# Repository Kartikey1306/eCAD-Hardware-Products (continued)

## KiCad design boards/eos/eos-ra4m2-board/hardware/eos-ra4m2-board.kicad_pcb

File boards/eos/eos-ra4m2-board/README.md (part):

# EoS RA4M2 Board

An 80 × 170 mm, two-layer RA4M2 development board with Uno R3 shield sockets,
SPI and I²C Pmod ports, a GPIO access header, USB device, USB-UART and SWD.
Designed by Kartikeydheer Srivastava.
All rights reserved: not open source, and not under this repository's MIT licence.
Anyone may view it, clone this repository and run its tests; anything more needs
Kartikeydheer Srivastava's written permission (kartikeydheer@gmail.com). EmbeddedOS (EoS) Research Foundation has a limited, revocable
permission. See [LICENSE.txt](LICENSE.txt) and [the licence summary](../README.md#licence).

A board for the same job as Renesas EK-RA4M2; an original design, not a copy:
no design file of the vendor's was used; the header positions come from the
published Uno R3 relative dimensions in Matthew Beckler's dimension drawing
v1.05 and Digilent's Pmod Interface Specification 1.3.0, with original placement
on the board. The 80 × 170 mm overall dimensions come from the EK-RA4M2 user
manual, R20UT4815EG0100 §3. Its mounting and connector coordinates are not
dimensioned there, so this board does not claim enclosure or mounting-pattern
compatibility. The MCU assignments are original and require their own firmware
configuration.

| Top | Bottom |
|---|---|
|  |  |

## What is on it

| Block | Parts, values and source |
|---|---|
| MCU | Renesas R7FA4M2AD3CFP, Cortex-M33, 100 MHz, 512 KB code flash, 8 KB data flash, 128 KB SRAM, LQFP-100. Pins: R01DS0367EJ0150 Table 1.17, LQFP100 column. |
| Digital supply | 100 nF at each VCC pin and VCC_USB; 220 nF C0G at VCL; VBATT tied to 3.3 V. R01UH0892 Table 45.1 and R01AN5988 Table 1. |
| Analog supply | Bourns MH1608-221Y 220 Ω ferrite; 10 µF + 10 nF bulk/filter capacitors, 100 nF at AVCC0 and VREFH0; VREFH also tied to this supply. R01UH0892 Figure 37.34. |
| Clocks | NDK NX3225GA 16 MHz, CL 8 pF, with two 6 pF loads; Abracon ABS07 32.768 kHz, CL 9 pF, with two 15 pF loads. R01AN7202 Rev.1.02 Group 1 Tables 4.1.1/4.2.1; select 8.1–16 MHz main drive and standard CL sub-clock drive. |
| Device USB (J1) | RA4M2 USBFS, USB-C sink, 5.1 kΩ on each CC pin, 27 Ω on D+/D−, SP0503BAHTG ground-only ESD and 500 mA PTC. VBUS sense uses 18 kΩ/30 kΩ plus 1 µF, adapted from R01UH0892 Figure 26.3 for a 5.5 V maximum input. |
| Debug USB (J2) | CP2102N-A02-GQFN24 on SCI9 P109/P110, also the ROM serial boot pins. Powered by board 3.3 V with VREGIN tied to VDD; 100 nF local bypass and 4.7 µF bulk capacitors, 1 kΩ reset pull-up. VBUS divider 22.1 kΩ/47.5 kΩ and 5.1 kΩ bleed; SP0503BAHTG ESD. CP2102N data sheet Figures 2.3/2.6, R01UH0892 Table 44.27. |
| Power selection | TPS2116 prefers J2, otherwise J1, with reverse blocking between ports. 27 kΩ/10 kΩ PR1 divider, MODE to VIN1, 1 µF per input and 100 µF polymer output. TI SLVSFG1A §§7.3.4, 7.6.1.1 and 9. |
| Regulator | TPS7A9101, 3.57 kΩ/1.15 kΩ feedback for nominal 3.283 V, 22 µF input, 10 µF output, 10 nF NR/SS for calculated 0.80–2.2 ms ramp. TI SBVS282A Table 7-1, Equation 6 and §7.1.3; RA4M2 Table 2.9. |
| Debug and boot | Standard Arm 10-pin SWD header J9, replacing the proprietary on-board probe. 10 kΩ RES/NMI pull-ups, reset button, no reset capacitor. JP1 grounds MD through 1.5 kΩ for boot mode; otherwise its internal pull-up selects normal execution. R20UT4686 Figures 2.7/2.9 and R01AN5988 §§3/6. |
| User interface | User button P408/IRQ7 with 10 kΩ pull-up; red P409, green P410 and yellow P411 LEDs, about 2 mA each using 750/680/680 Ω. Green supply LED uses 680 Ω. Kingbright DSAO7432/7433/7434. |
| Expansion | Uno R3 sockets, Type 2A SPI Pmod and Type 6A I²C Pmod; 2.2 kΩ I²C pull-ups, removable by cutting JP2. TI SLVA689A gives 161 pF maximum bus capacitance for 400 kHz with these pulls. J10 exposes 33 remaining GPIOs. |

Both USB ports and the MCU share the same 3.3 V supply. The UART bridge therefore
cannot be unpowered while MCU TX is driven. Its separate VBUS sense prevents an
asserted USB pull-up after its cable is unplugged. The ground-only ESD parts do
not create a D+ to VBUS path. Configure CP2102N descriptors and MCU USB firmware
for the board's actual power consumption.

The device-port divider produces at most 3.47 V at 5.5 V with 1% resistor
extremes, below the MCU's 3.6 V limit when VCC is absent. At 4.4 V it produces at
least 2.729 V, above the worst-case 2.658 V input-high threshold for this supply.

## Headers and firmware

All logic is **3.3 V**. J5's 3V3, IOREF and 5V pins, both Pmod supplies and J10's
3V3 pins are outputs. Do not apply external power through them. AREF and VIN are
unconnected. Do not drive GPIOs while the board is unpowered.

| Shield signal | RA4M2 port/function |
|---|---|
| D0, D1 | P113 RXD2, P112 TXD2 |
| D2, D3, D4 | P111, P114 GTIOC2B, P609 |
| D5, D6, D7 | P608 GTIOC4B, P115 GTIOC4A, P610 |
| D8, D9, D10 | P603, P602 GTIOC7B, P103 |
| D11, D12, D13 | P101 MOSI0, P100 MISO0, P102 SCK0 (SCI0 simple SPI) |
| SDA, SCL | P401 SDA0_A, P400 SCL0_A (IIC0) |
| A0–A5 | P005–P000, respectively (AN005–AN000) |

J3, pin 1 to 10: D8, D9, D10, D11, D12, D13, GND, AREF (open), SDA, SCL.
J4, pin 1 to 8: D0–D7. J5, pin 1 to 8: NC, IOREF, RESET, 3V3, 5V, GND, GND,
VIN (open). J6, pin 1 to 6: A0–A5.

| Pmod pin | J7 Type 2A SPI | J8 Type 6A I²C |
|---|---|---|
| 1 | P500, GPIO chip select | P403, interrupt |
| 2 | P101, MOSI0 | P402, reset |
| 3 | P100, MISO0 | P400, SCL0_A |
| 4 | P102, SCK0 | P401, SDA0_A |
| 5, 11 | GND | GND |
| 6, 12 | 3V3 | 3V3 |
| 7 | P501, interrupt | P404 |
| 8 | P502, reset | P405 |
| 9 | P503, second chip select | P505 |
| 10 | P504, third chip select | NC |

Pmod numbering differs from KiCad's odd/even connector-pad numbering. These
are the Pmod mating pin numbers; the schematic part description records the
pad conversion. Each socket's square pad is the footprint's pad 1, which is
Pmod pin 6 (3V3), not Pmod pin 1. Pmod pin 1 is pad 11, marked by a silkscreen
"1" beside it. The SPI and I²C signals are shared with the shield sockets.
Avoid two peripherals using the same chip-select or I²C address.

J9 uses the standard Cortex Debug SWD pinout: 1 VTref, 2 SWDIO/P108, 3 GND,
4 SWCLK/P300, 5 GND, 6 SWO/P109, 7 key/open, 8 open, 9 GND detect, 10 RES.
SWO and the UART's TXD9 share P109: select one function in firmware. SWO trace
bytes can reach the UART receiver when trace is selected; this is not a second
independent console.

J9 follows the Arm pinout, not Renesas's combined debug and serial pinout
(R01UH0892 Table 44.32), which puts P201/MD on pin 4 and P110/RXD9 on pin 8. SWD
on J9 flashes and debugs the MCU. The TrustZone IDAU boundary settings can be
written only through the serial programming interface (R01UH0892 §44), so an
E2 or E2 Lite on J9 cannot set them. To program them, fit JP1, reset the board,
and run Renesas Flash Programmer over the CP2102N on J2 in SCI boot mode.

J10 follows ordinary odd/even 2×20 numbering, pin 1 marked on the PCB:

| Odd pin | Signal | Even pin | Signal |
|---:|---|---:|---|
| 1 | P006 | 2 | P007 |
| 3 | P008 | 4 | P013 |
| 5 | P014 | 6 | P015 |
| 7 | P406 | 8 | P412 |
| 9 | P413 | 10 | P414 |
| 11 | P415 | 12 | P708 |
| 13 | P104 | 14 | P105 |
| 15 | P106 | 16 | P107 |
| 17 | P600 | 18 | P601 |
| 19 | P205 | 20 | P206 |
| 21 | P207 | 22 | P208 |
| 23 | P209 | 24 | P210 |
| 25 | P211 | 26 | P214 |
| 27 | P301 | 28 | P302 |
| 29 | P303 | 30 | P304 |
| 31 | P305 | 32 | P306 |
| 33 | P307 | 34 | GND |
| 35 | 3V3 | 36 | GND |
| 37 | 3V3 | 38 | GND |
| 39 | 3V3 | 40 | GND |

J10 pins 1–6 are PORT0 pins (P006, P007, P008, P013, P014, P015). While the
ADC's high-precision channels are in use, do not use PORT0 pins as digital
outputs (R01UH0892 §37.6.12). A0–A5 are on P000–P005, also PORT0.

Hold RESET, fit JP1, then release RESET to enter SCI/USB boot mode; remove JP1
and reset to run the application. The board includes no automatic DTR reset.

J9 and JP1 sit right of the Uno shield outline (x > 68.58 mm from the left
edge), so a fitted shield covers neither. The RESET and USER buttons (SW1, SW2)
and the user LEDs D2–D4 lie under a fitted shield. With a shield on, reset
through the shield's own RESET (J5 pin 3 is RES) or through J9 pin 10.

## Power budget

C5 is [Murata GRM31C5C1H224JE02L](https://www.murata.com/en-us/products/productdetail?partno=GRM31C5C1H224JE02%23),
220 nF, ±5%, 50 V C0G, 1206. This retains the nominal value specified for VCL
without the large voltage-dependent loss of the original X7R part. Murata's
[DC-bias guidance](https://www.murata.com/en-eu/support/faqs/capacitor/ceramiccapacitor/char/0005)
distinguishes C0G from high-permittivity ceramics. The MCU manual does not state
an allowed effective-capacitance interval; regulator stability remains a
prototype check.

C22 is polarized [Panasonic 16SVPC100M](https://industrial.panasonic.com/ww/products/pt/OS-CON/models/16SVPC100M),
100 µF, ±20%, 16 V polymer, 24 mΩ ESR, replacing the nominal 100 µF ceramic whose
typical model fell to about 38 µF at 5.5 V. The initial tolerance floor is 80 µF;
including the SVPC series' 20% endurance-change limit gives 64 µF at the
specified measurement conditions. TPS2116 §7.3.4 recommends about 100 µF;
it does not specify a guaranteed minimum for every load. Transient performance
must therefore be checked with the actual cables and loads. Fit pad 1 to +5V
and pad 2 to ground. Its body (x 69.4–76.0 mm) lies outside the Uno shield
outline (x ≤ 68.58 mm); its 5.9 mm height matters only for an enclosure.

TPS2116 §8.2.2 estimates capacitor charging current as C × V / soft-start time.
At 5 V and the typical 1.7 ms ramp, C22 alone draws about 294 mA nominal or
353 mA at +20% capacitance, and C23 (22 µF) adds about 65 mA nominal. The
regulator then charges about 30 µF on 3.3 V (C24, C9, C18, C19 and nine 100 nF
capacitors) over its 0.80–2.2 ms soft start, 45–124 mA; the two ramps can
overlap. The ramp is not a guaranteed minimum, and the mux is not a USB current
limiter. The +5V side alone stores about 0.6 mC (122 µF at 5 V), about 12
times what the 10 µF that USB 2.0 §7.2.4.1 allows a device to present would
hold, and the 3.3 V side adds about 0.1 mC; the TPS2116 slew spreads the
current, not the charge. USB-IF inrush compliance is therefore not expected,
and these numbers do not establish a 500 mA total peak. Validate startup
current, suspend, switchover and output overshoot on a prototype.

The expansion connectors share **150 mA total**, across all 3.3 V and 5 V pins;
the limit is not per connector. A 120 mA board allowance makes the steady-state
budget 270 mA; it excludes capacitor charging during startup.
The allowance covers 65 mA maximum digital MCU consumption and 10 mA USB
consumption (RA4M2 Table 2.7), analog circuits, CP2102N, LEDs and pull-ups.

At 270 mA, the fuse's specified 0.70 Ω post-trip resistance gives 0.189 V loss
and the mux's 60 mΩ maximum gives 0.016 V. The fuse holds 420 mA at 40 °C,
above this budget, and a configured 500 mA USB source has margin. Before USB
enumeration, firmware must keep the entire load below the default unit-load
limit; expansions must be disconnected or held inactive. USB suspend behavior,
inrush and source switchover need bench validation.

With every expansion load on 3.3 V and 5.5 V input, the LDO dissipates about
0.60 W. Its 62.5 °C/W figure is for a JEDEC multilayer test board and predicts a
37.5 °C rise. This two-layer board, with no via in the thermal pad, will run
hotter by an amount not measured, so check the regulator's temperature in that
case on a prototype. The regulator's 1 A silicon rating is not this board's
expansion allowance. The supply ramp is calculated, not measured.

## Parts notes

- Every resistor without a named part (all but R18 and R19) is generic: 1%,
  0402, thick film, rated 62.5 mW or more. The largest dissipation is about
  6 mW (R15 at 5.5 V), so any vendor's part meeting that line will do.
- JP1 is a [Samtec TSW-102-07-G-S](https://www.samtec.com/products/tsw-102-07-g-s)
  1×2 2.54 mm header, fitted with a
  [Samtec SNT-100-BK-G](https://www.samtec.com/products/snt-100-bk-g) shunt.
- C1 is a [Samsung CL31B104KBCNNNC](https://www.lcsc.com/product-detail/C24497.html),
  100 nF ±10% 50 V X7R 1206; the 1206 body lets the 16 MHz crystal lines pass
  between its pads (see Layout).
- C22's lifecycle status is unknown: Panasonic's page gives no lifecycle field.
  A second source in the same C6 land must match its ESR and ripple-current
  rating; none has been checked.

## Not on this board

- Renesas/SEGGER's on-board J-Link probe and debug-out function: replaced by the
  external SWD header and CP2102N UART.
- USB host/OTG source power, QSPI memory, capacitive-touch electrode, mikroBUS,
  Grove and Qwiic sockets: no implementation is claimed. I²C and spare MCU
  signals are available on the documented headers.
- Battery backup, MCU current-measurement jumpers, a perfboard grid and 20-pin
  ETM/JTAG trace. VBATT follows the main 3.3 V supply.
- Vendor connector placement, mounting pattern, firmware examples and debugger
  firmware. Only the published overall outline and expansion standards are
  retained.
- I²C on A4/A5. P001 and P000 have no IIC function (R01DS0367 Table 1.17), so
  older shields that take I²C from A4/A5 (the Uno R3 bridges them to SDA/SCL)
  will not work; I²C is on the SDA/SCL pins only.
- A 2×3 ICSP header. Shields that take SPI only from ICSP get none; SPI is on
  D11–D13 (SCI0 simple SPI).
- An interrupt on D3. P114 has no IRQ function (Table 1.17, pin 57), where the
  Uno's D3 is INT1. D2 (P111) is IRQ4.

## Layout

- **Oscillators** (R01AN7202 §6.1). The bottom pin row runs VCL 9, XCIN 10,
  XCOUT 11, VSS 12, XTAL 13, EXTAL 14, VCC 15. VSS 12 drops straight onto C5's
  ground pad and on to C1's: a ground spine between the two oscillators. C5
  (VCL) and C1 (VCC) are 1206 parts whose bodies straddle the clock pairs,
  XCIN/XCOUT under C5 and XTAL/EXTAL under C1, so both ground pads sit on the
  spine. Between the pads the clock lines keep 0.20 mm from them (0.63 mm from
  C1's supply pad). The clock lines are 0.15 mm, on the top layer, with no via:
  XTAL 9.2 mm, EXTAL 7.4 mm, XCIN 6.4 mm and XCOUT 5.5 mm from pin to crystal
  pad. No other net crosses them or lies inside either crystal's courtyard, on
  either layer, and no other net's track runs under the clock-side pins 9–15.
  The bottom layer under those pins, the clock lines and both crystals, to
  beyond the load capacitors, is kept free of tracks, so its ground pour is
  solid there. A top-layer keep-out keeps other lines off the 32.768 kHz
  crystal's outer side.
- **VSS 12 and the oscillator ground.** A 0.15 mm top-layer line runs from pin
  12's inner end under the MCU to VSS 63 (14.7 mm), and VSS 83, VSS 45 and
  VSS_USB 26 each have a line inward to it. VSS 12 reaches the other VSS pins
  through 10.7–16.0 mm of ground copper. The oscillator ground (the spine and
  the crystals' and load capacitors' ground pads) is part of the board's main
  top ground pour. It joins the rest of ground at VSS 12, through the pour
  around the oscillator area (openings up to 7.75 mm wide), and through the nine
  vias that tie the bottom pour under the crystals to it. So no single track or
  via carries it, but it is not isolated as a shield; see below.
- **Accepted for rev A, near the oscillators** (R01AN7202 §6.1):
  - EXTAL runs 0.20 mm from the VCC 15 → C1 supply line for 2.8 mm, beyond the
    pad row (§6.1.4 asks that no adjacent line run beside a clock line).
  - Between C1's and C5's pads, each clock pair is 0.20 mm apart: XTAL/EXTAL
    for 4.6 mm and XCIN/XCOUT for 1.5 mm (§6.1.1(4) asks for at least 0.3 mm).
    That adds roughly 0.15 pF across the main crystal, small against its
    load.
  - XCIN passes 0.20 mm from C5's VCL pad for 1.0 mm; VCL escapes outward
    beside it rather than under the MCU.
  - The oscillator ground is not an isolated shield. The main and sub-clock
    grounds are one fill, that fill is the board's main top pour, and it also
    carries C1's and C5's decoupling return. §6.1.2 shows separate shields that
    branch from ground at the VSS pin, and §6.2(5) warns that a shield not
    isolated there carries the MCU's current. A later revision could ring the
    shield with a top-layer keep-out open only at pin 12.
  - The VSS 12 lines and the shield spine are 0.15 mm; the generator can't yet
    give one route a wider track.
- **Decoupling.** Each MCU decoupling capacitor has a ground line from its VSS
  pin beside its supply line. Ground copper from pad to pin: C1 4.6 mm, C2 2.1,
  C3 1.8, C4 2.7, C5 2.3, C6 4.4 (it crosses under the USB pair through two
  vias), C7 2.5 and C8 2.9 mm. The CP2102N's 100 nF capacitors reach its
  exposed pad's vias through a patch of bottom pour kept free of tracks: C16
  4.3 mm and C17 4.4 mm. C1's supply side is 5.2 mm, longer than the others,
  because its 1206 supply pad sits beyond the main-crystal lines.
- **CP2102N 4.7 µF capacitors.** C19 sits 3.5 mm (centre to pin) from VREGIN
  and C18 4.5–5.2 mm from the VIO, VDD and VREGIN pins, each joined on the top
  layer with no via. C16, C17, the reset and VBUS-sense resistors and the debug
  USB pair take the nearer places; this placement is accepted.
- **USB device pair.** The trunk leaves J1's B row, where D+ lies above D− as at
  the MCU, so the pair never crosses itself. Both lines run on the top layer
  with no via, and the A-row contacts join round either side.
- **ESD parts.** U2's common pin has a ground via 1.0 mm away. U3's has a ground
  line to J2's ground contacts, with a via beside each end.
- **Debug lines.** The RES pull-up R1 sits 2.7 mm of track from pin 38. With J9
  and JP1 beyond the shield outline, MD, SWDIO and SWCLK run 46–48 mm, and RES
  65 mm from J9 and 74 mm from the shield's reset pin J5.3, mostly on the
  bottom layer.
- **CP2102N supply.** Its 3.3 V comes straight from the regulator's output
  capacitor C24: 24.5 mm of copper from U5's output to VDD.
- **3.3 V to the MCU and the shield.** From U5's output the copper runs 77 mm
  to VCC 15 and 75 mm to VBATT 8, each with two vias, and 101 mm to the
  shield's 3.3 V pin J5.4. These are DC feeds: C1's supply line to VCC 15 is
  still 5.2 mm.
- **USB return paths.** Bottom-layer tracks cross under the device USB pair at
  38 points from 19 nets, and a 3.3 V track runs along D− on the bottom layer,
  within 0.3 mm of it, for about 4 mm. Other tracks cross the debug pair at 6
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
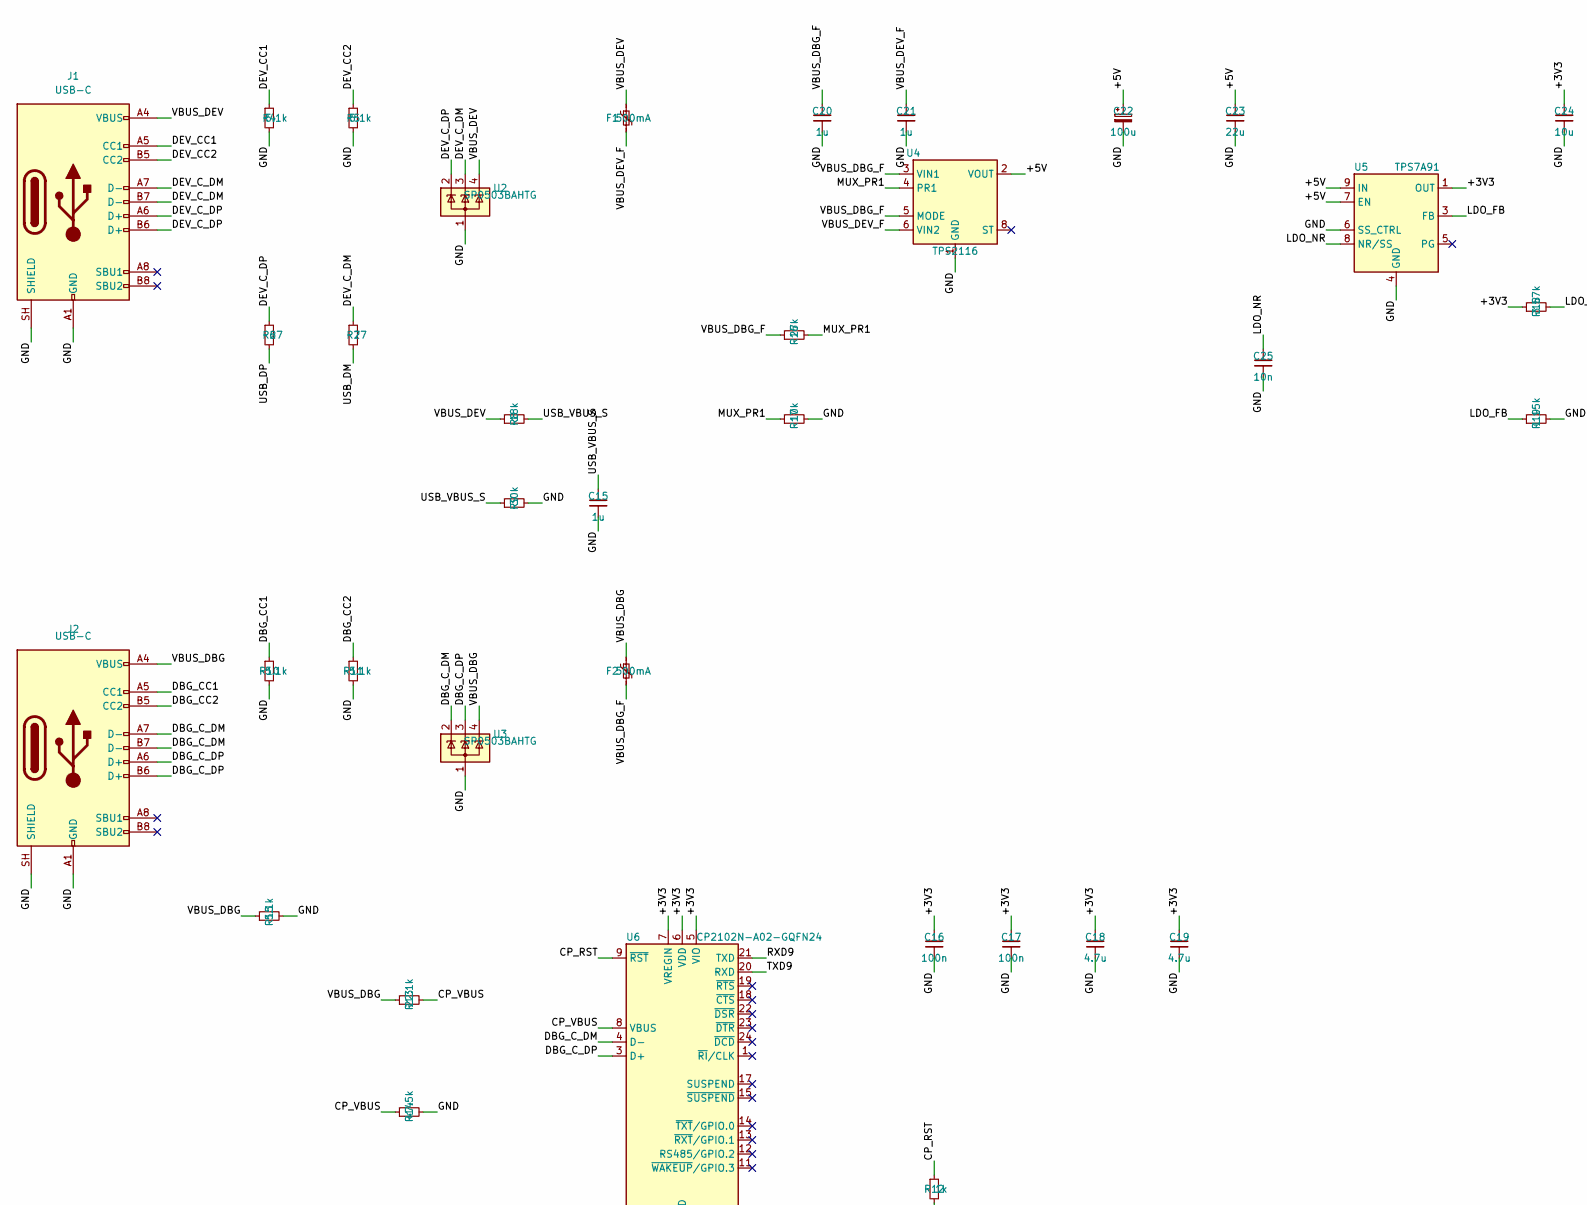
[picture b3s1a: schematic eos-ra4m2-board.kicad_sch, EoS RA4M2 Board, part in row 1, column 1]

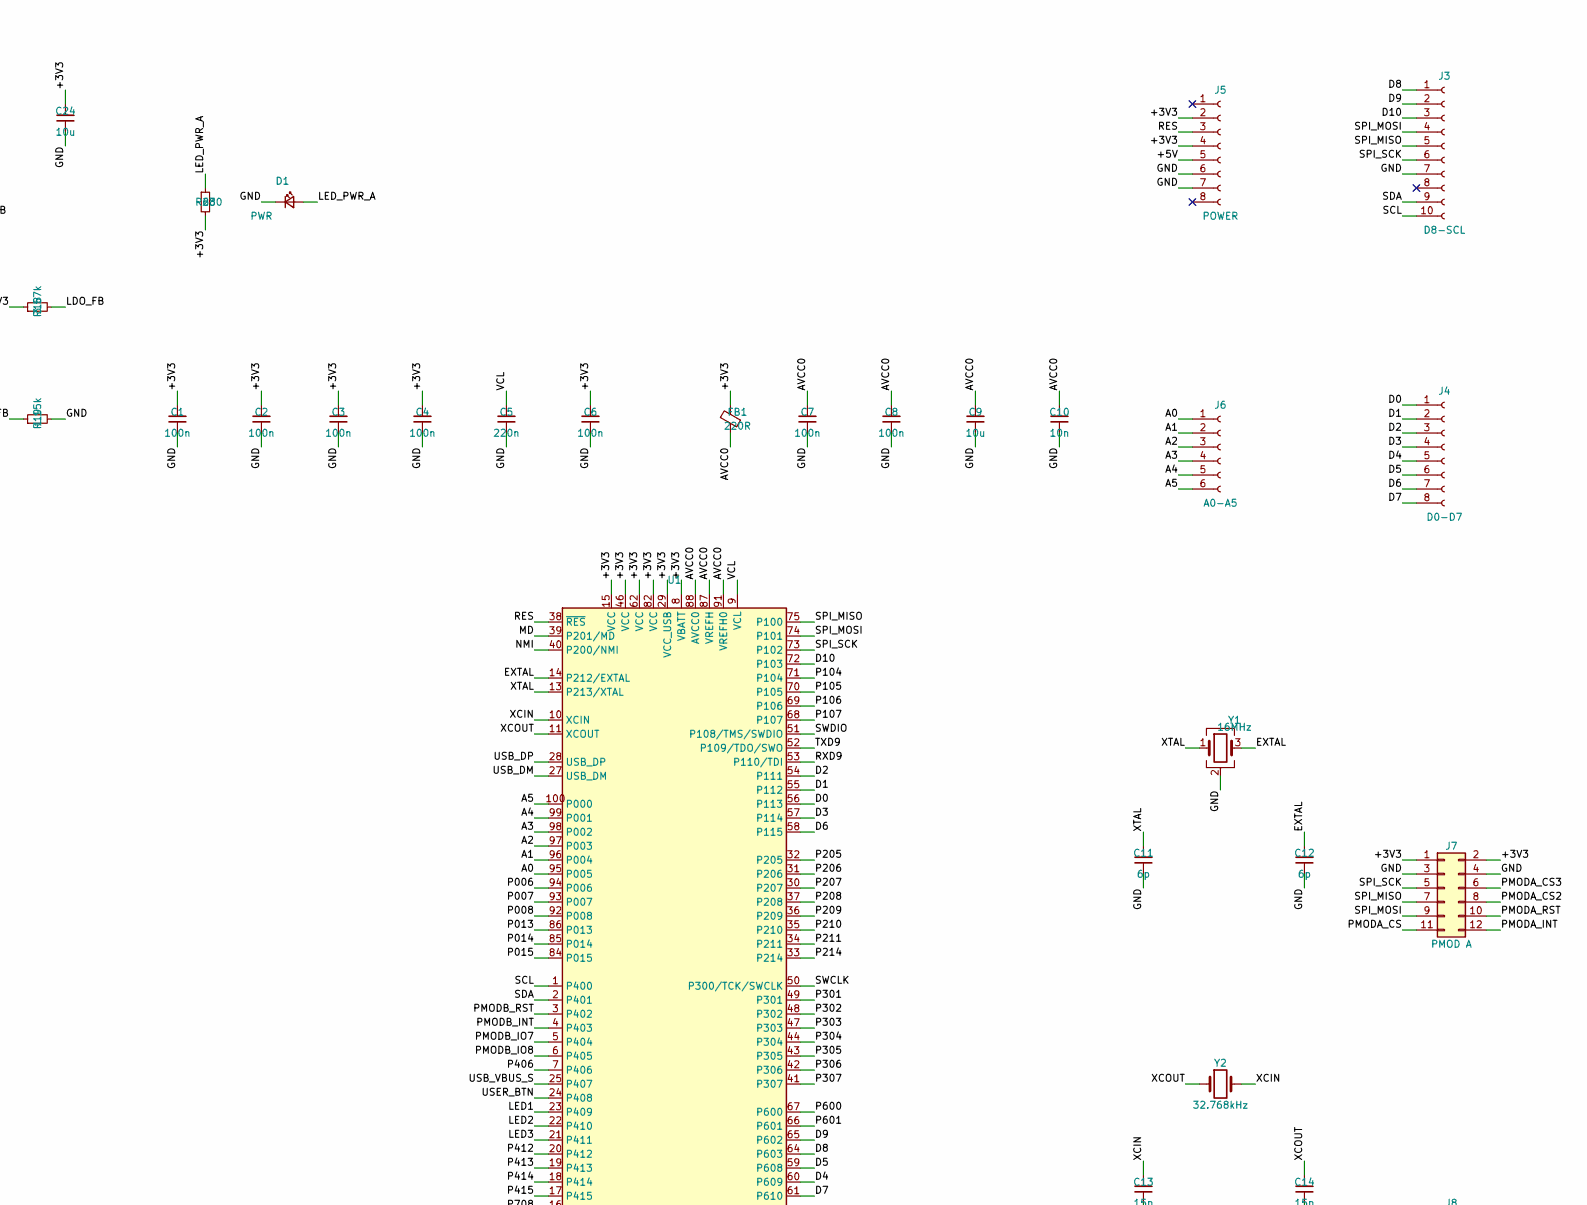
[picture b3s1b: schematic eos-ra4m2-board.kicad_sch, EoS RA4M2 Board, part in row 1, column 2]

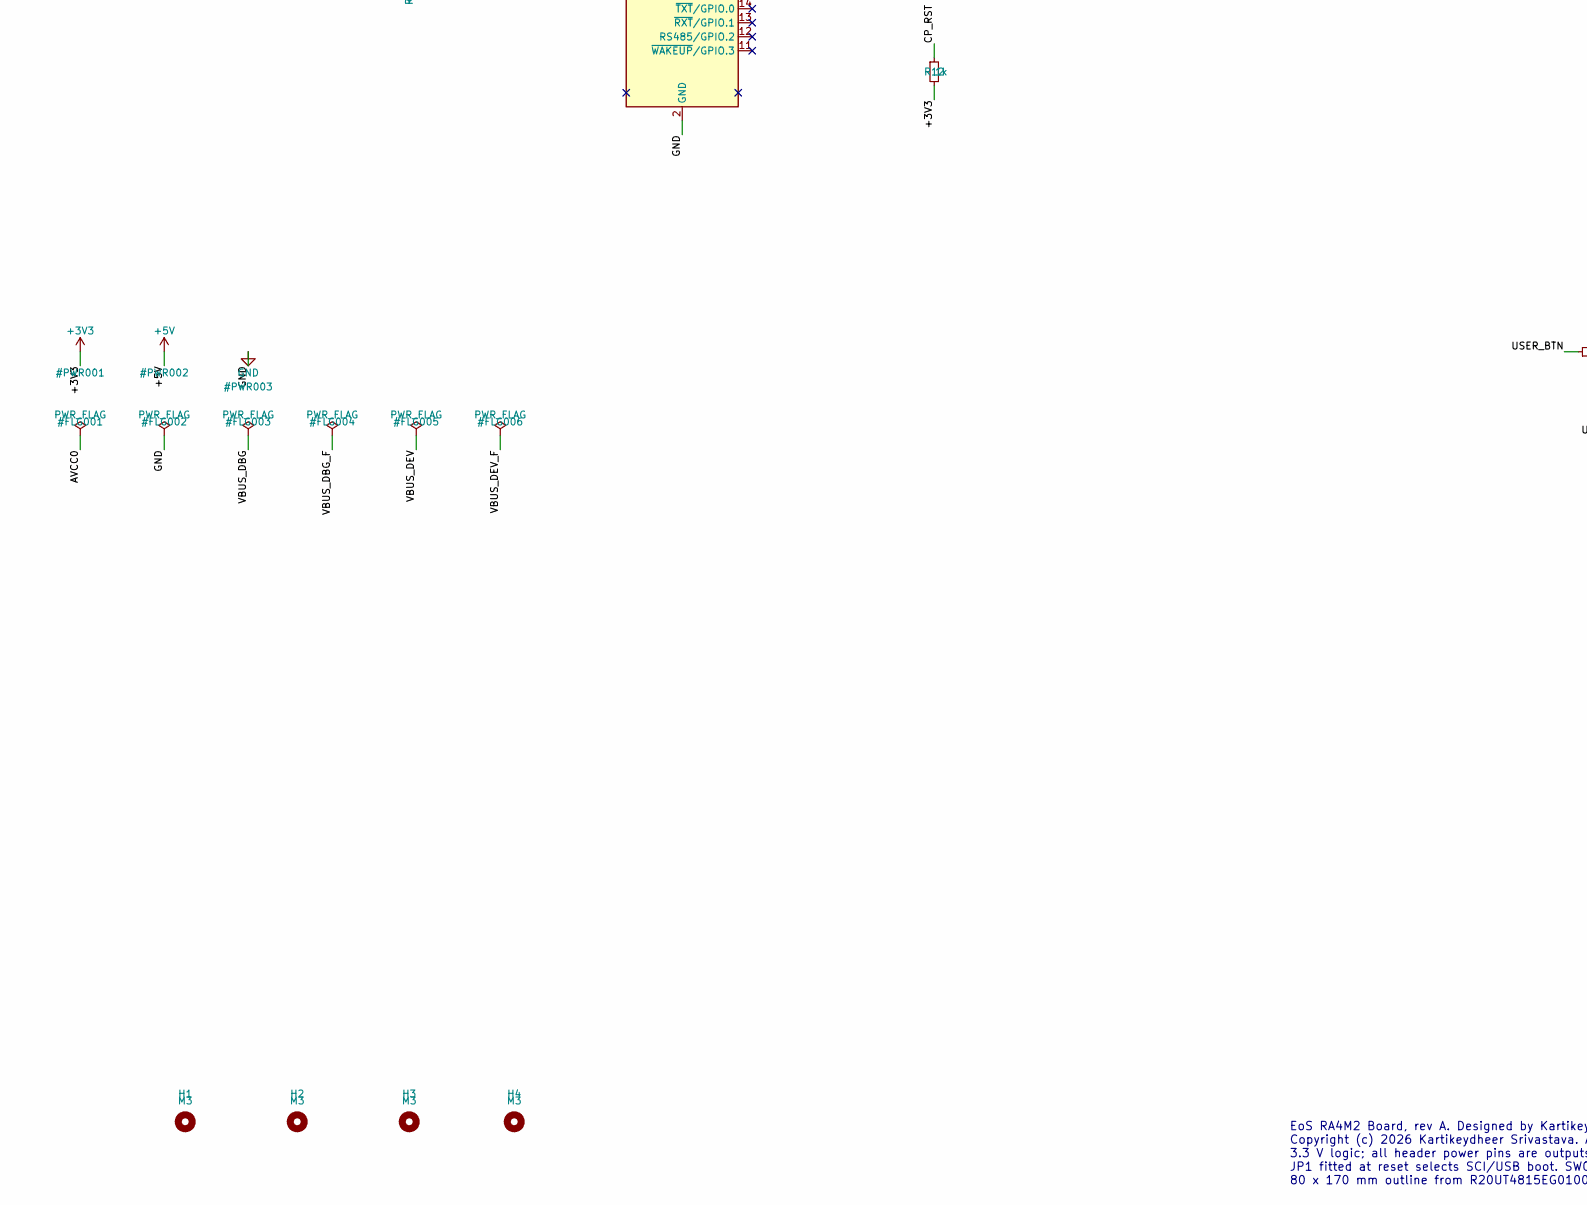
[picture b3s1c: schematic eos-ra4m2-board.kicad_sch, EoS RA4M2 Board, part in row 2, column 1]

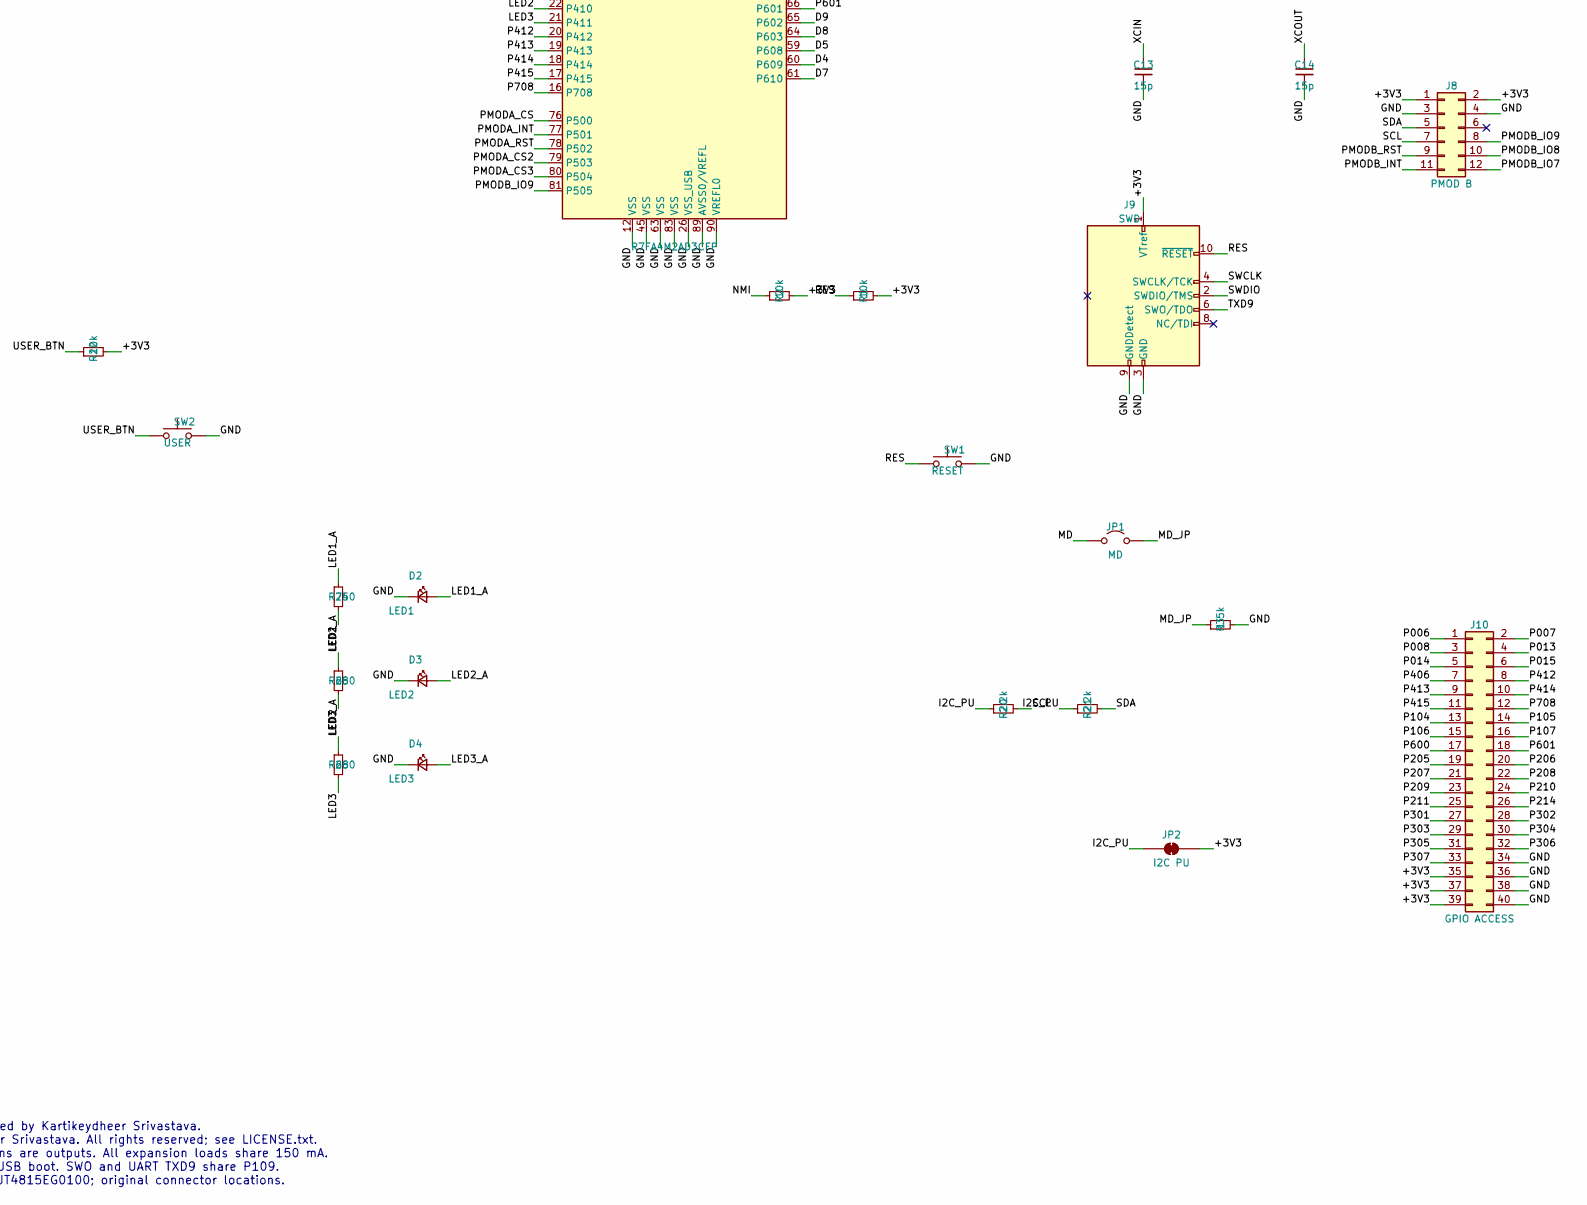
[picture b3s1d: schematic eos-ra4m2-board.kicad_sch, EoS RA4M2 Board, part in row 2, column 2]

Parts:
C1: 100n; C_1206_3216Metric; MPN CL31B104KBCNNNC
C2, C3, C4, C6, C7, C8, C16, C17: 100n; C_0402_1005Metric; MPN CL05B104KO5NNNC
C5: 220n; C_1206_3216Metric; MPN GRM31C5C1H224JE02L
C9: 10u; C_0603_1608Metric; MPN GRM188R61A106KE69D
C10, C25: 10n; C_0402_1005Metric; MPN GRM155R71H103KA88D
C11, C12: 6p; C_0402_1005Metric; MPN GRM1555C1H6R0DA01D
C13, C14: 15p; C_0402_1005Metric; MPN GRM1555C1H150JA01D
C15, C20, C21: 1u; C_0603_1608Metric; MPN GRM188R71C105KA12D
C18, C19: 4.7u; C_0603_1608Metric; MPN GRM188R61A475KE15D
C22: 100u; CP_Elec_6.3x5.9; MPN 16SVPC100M
C23: 22u; C_0805_2012Metric; MPN GRM21BR61A226ME51L
C24: 10u; C_0805_2012Metric; MPN GRM21BR61C106KE15L
D1: PWR; LED_0603_1608Metric; MPN APTD1608LCGCK
D2: LED1; LED_0603_1608Metric; MPN APTD1608LSURCK
D3: LED2; LED_0603_1608Metric; MPN APTD1608LCGCK
D4: LED3; LED_0603_1608Metric; MPN APTD1608LSYCK
F1, F2: 500mA; Fuse_1206_3216Metric; MPN 1206L050YR
FB1: 220R; L_0603_1608Metric; MPN MH1608-221Y
H1, H2, H3, H4: M3; MountingHole_3.2mm_M3_ISO14580
J1, J2: USB-C; USB_C_Receptacle_HRO_TYPE-C-31-M-12; MPN TYPE-C-31-M-12
J3: D8-SCL; PinSocket_1x10_P2.54mm_Vertical; MPN SSW-110-01-T-S
J4: D0-D7; PinSocket_1x08_P2.54mm_Vertical; MPN SSW-108-01-T-S
J5: POWER; PinSocket_1x08_P2.54mm_Vertical; MPN SSW-108-01-T-S
J6: A0-A5; PinSocket_1x06_P2.54mm_Vertical; MPN SSW-106-01-T-S
J7: PMOD A; PinSocket_2x06_P2.54mm_Horizontal; MPN PPPC062LJBN-RC
J8: PMOD B; PinSocket_2x06_P2.54mm_Horizontal; MPN PPPC062LJBN-RC
J9: SWD; PinHeader_2x05_P1.27mm_Vertical_SMD; MPN FTSH-105-01-L-DV-K
J10: GPIO ACCESS; PinHeader_2x20_P2.54mm_Vertical; MPN TSW-120-07-G-D
JP1: MD; PinHeader_1x02_P2.54mm_Vertical; MPN TSW-102-07-G-S
JP2: I2C PU; SolderJumper-2_P1.3mm_Bridged_RoundedPad1.0x1.5mm
R1, R2, R17, R22: 10k; R_0402_1005Metric
R3: 1.5k; R_0402_1005Metric
R4, R5, R10, R11, R15: 5.1k; R_0402_1005Metric
R6, R7: 27; R_0402_1005Metric
R8: 18k; R_0402_1005Metric
R9: 30k; R_0402_1005Metric
R12: 1k; R_0402_1005Metric
R13: 22.1k; R_0402_1005Metric
R14: 47.5k; R_0402_1005Metric
R16: 27k; R_0402_1005Metric
R18: 3.57k; R_0402_1005Metric; MPN ERA-2AEB3571X
R19: 1.15k; R_0402_1005Metric; MPN ERA-2AEB1151X
R20, R21: 2.2k; R_0402_1005Metric
R23, R25, R26: 680; R_0402_1005Metric
R24: 750; R_0402_1005Metric
SW1: RESET; SW_Push_1P1T_NO_CK_KMR2; MPN KMR221G LFS
SW2: USER; SW_Push_1P1T_NO_CK_KMR2; MPN KMR221G LFS
U1: R7FA4M2AD3CFP; LQFP-100_14x14mm_P0.5mm; MPN R7FA4M2AD3CFP#AA0
U2, U3: SP0503BAHTG; SOT-143; MPN SP0503BAHTG
U4: TPS2116; SOT-583-8; MPN TPS2116DRLR
U5: TPS7A91; Texas_S-PDSO-N10_EP1.2x2mm; MPN TPS7A9101DSKR
U6: CP2102N-A02-GQFN24; QFN-24-1EP_4x4mm_P0.5mm_EP2.6x2.6mm; MPN CP2102N-A02-GQFN24R
Y1: 16MHz; Crystal_SMD_3225-4Pin_3.2x2.5mm; MPN NX3225GA-16.000M-STD-CRG-2
Y2: 32.768kHz; Crystal_SMD_3215-2Pin_3.2x1.5mm; MPN ABS07-32.768KHZ-9-T

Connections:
+3V3: C1.1, C2.1, C3.1, C4.1, C6.1, C16.1, C17.1, C18.1, C19.1, C24.1, FB1.1, J5.2, J5.4, J7.1, J7.2, J8.1, J8.2, J9.1 (VTref), J10.35, J10.37, J10.39, JP2.2 (B), R1.2, R2.2, R12.2, R18.1, R22.2, R23.2, U1.8 (VBATT), U1.15 (VCC), U1.29 (VCC_USB), U1.46 (VCC), U1.62 (VCC), U1.82 (VCC), U5.1 (OUT), U5.2 (OUT), U6.5 (VIO), U6.6 (VDD), U6.7 (VREGIN)
+5V: C22.1, C23.1, J5.5, U4.2 (VOUT), U4.7 (VOUT), U5.7 (EN), U5.9 (IN), U5.10 (IN)
/A0: J6.1, U1.95 (P005)
/A1: J6.2, U1.96 (P004)
/A2: J6.3, U1.97 (P003)
/A3: J6.4, U1.98 (P002)
/A4: J6.5, U1.99 (P001)
/A5: J6.6, U1.100 (P000)
/AVCC0: C7.1, C8.1, C9.1, C10.1, FB1.2, U1.87 (VREFH), U1.88 (AVCC0), U1.91 (VREFH0)
/CP_RST: R12.1, U6.9 (~RST)
/CP_VBUS: R13.2, R14.1, U6.8 (VBUS)
/D0: J4.1, U1.56 (P113)
/D1: J4.2, U1.55 (P112)
/D2: J4.3, U1.54 (P111)
/D3: J4.4, U1.57 (P114)
/D4: J4.5, U1.60 (P609)
/D5: J4.6, U1.59 (P608)
/D6: J4.7, U1.58 (P115)
/D7: J4.8, U1.61 (P610)
/D8: J3.1, U1.64 (P603)
/D9: J3.2, U1.65 (P602)
/D10: J3.3, U1.72 (P103)
/DBG_CC1: J2.A5 (CC1), R10.1
/DBG_CC2: J2.B5 (CC2), R11.1
/DBG_C_DM: J2.A7 (D-), J2.B7 (D-), U3.2 (K), U6.4 (D-)
/DBG_C_DP: J2.A6 (D+), J2.B6 (D+), U3.3 (K), U6.3 (D+)
/DEV_CC1: J1.A5 (CC1), R4.1
/DEV_CC2: J1.B5 (CC2), R5.1
/DEV_C_DM: J1.A7 (D-), J1.B7 (D-), R7.1, U2.3 (K)
/DEV_C_DP: J1.A6 (D+), J1.B6 (D+), R6.1, U2.2 (K)
/EXTAL: C12.1, U1.14 (P212/EXTAL), Y1.3
/I2C_PU: JP2.1 (A), R20.1, R21.1
/LDO_FB: R18.2, R19.1, U5.3 (FB)
/LDO_NR: C25.1, U5.8 (NR/SS)
/LED1: R24.2, U1.23 (P409)
/LED1_A: D2.2 (A), R24.1
/LED2: R25.2, U1.22 (P410)
/LED2_A: D3.2 (A), R25.1
/LED3: R26.2, U1.21 (P411)
/LED3_A: D4.2 (A), R26.1
/LED_PWR_A: D1.2 (A), R23.1
/MD: JP1.1 (A), U1.39 (P201/MD)
/MD_JP: JP1.2 (B), R3.1
/MUX_PR1: R16.2, R17.1, U4.4 (PR1)
/NMI: R2.1, U1.40 (P200/NMI)
/P006: J10.1, U1.94 (P006)
/P007: J10.2, U1.93 (P007)
/P008: J10.3, U1.92 (P008)
/P013: J10.4, U1.86 (P013)
/P014: J10.5, U1.85 (P014)
/P015: J10.6, U1.84 (P015)
/P104: J10.13, U1.71 (P104)
/P105: J10.14, U1.70 (P105)
/P106: J10.15, U1.69 (P106)
/P107: J10.16, U1.68 (P107)
/P205: J10.19, U1.32 (P205)
/P206: J10.20, U1.31 (P206)
/P207: J10.21, U1.30 (P207)
/P208: J10.22, U1.37 (P208)
/P209: J10.23, U1.36 (P209)
/P210: J10.24, U1.35 (P210)
/P211: J10.25, U1.34 (P211)
/P214: J10.26, U1.33 (P214)
/P301: J10.27, U1.49 (P301)
/P302: J10.28, U1.48 (P302)
/P303: J10.29, U1.47 (P303)
/P304: J10.30, U1.44 (P304)
/P305: J10.31, U1.43 (P305)
/P306: J10.32, U1.42 (P306)
/P307: J10.33, U1.41 (P307)
/P406: J10.7, U1.7 (P406)
/P412: J10.8, U1.20 (P412)
/P413: J10.9, U1.19 (P413)
/P414: J10.10, U1.18 (P414)
/P415: J10.11, U1.17 (P415)
/P600: J10.17, U1.67 (P600)
/P601: J10.18, U1.66 (P601)
/P708: J10.12, U1.16 (P708)
/PMODA_CS: J7.11, U1.76 (P500)
/PMODA_CS2: J7.8, U1.79 (P503)
/PMODA_CS3: J7.6, U1.80 (P504)
/PMODA_INT: J7.12, U1.77 (P501)
/PMODA_RST: J7.10, U1.78 (P502)
/PMODB_INT: J8.11, U1.4 (P403)
/PMODB_IO7: J8.12, U1.5 (P404)
/PMODB_IO8: J8.10, U1.6 (P405)
/PMODB_IO9: J8.8, U1.81 (P505)
/PMODB_RST: J8.9, U1.3 (P402)
/RES: J5.3, J9.10 (~RESET), R1.1, SW1.1, U1.38 (~RES)
/RXD9: U1.53 (P110/TDI), U6.21 (TXD)
/SCL: J3.10, J8.7, R20.2, U1.1 (P400)
/SDA: J3.9, J8.5, R21.2, U1.2 (P401)
/SPI_MISO: J3.5, J7.7, U1.75 (P100)
/SPI_MOSI: J3.4, J7.9, U1.74 (P101)
/SPI_SCK: J3.6, J7.5, U1.73 (P102)
/SWCLK: J9.4 (SWCLK/TCK), U1.50 (P300/TCK/SWCLK)
/SWDIO: J9.2 (SWDIO/TMS), U1.51 (P108/TMS/SWDIO)
/TXD9: J9.6 (SWO/TDO), U1.52 (P109/TDO/SWO), U6.20 (RXD)
/USB_DM: R7.2, U1.27 (USB_DM)
/USB_DP: R6.2, U1.28 (USB_DP)
/USB_VBUS_S: C15.1, R8.2, R9.1, U1.25 (P407)
/USER_BTN: R22.1, SW2.1, U1.24 (P408)
/VBUS_DBG: F2.1, J2.A4 (VBUS), J2.A9 (VBUS), J2.B4 (VBUS), J2.B9 (VBUS), R13.1, R15.1, U3.4 (K)
/VBUS_DBG_F: C20.1, F2.2, R16.1, U4.3 (VIN1), U4.5 (MODE)
/VBUS_DEV: F1.1, J1.A4 (VBUS), J1.A9 (VBUS), J1.B4 (VBUS), J1.B9 (VBUS), R8.1, U2.4 (K)
/VBUS_DEV_F: C21.1, F1.2, U4.6 (VIN2)
/VCL: C5.1, U1.9 (VCL)
/XCIN: C13.1, U1.10 (XCIN), Y2.2
/XCOUT: C14.1, U1.11 (XCOUT), Y2.1
/XTAL: C11.1, U1.13 (P213/XTAL), Y1.1
GND: C1.2, C2.2, C3.2, C4.2, C5.2, C6.2, C7.2, C8.2, C9.2, C10.2, C11.2, C12.2, C13.2, C14.2, C15.2, C16.2, C17.2, C18.2, C19.2, C20.2, C21.2, C22.2, C23.2, C24.2, C25.2, D1.1 (K), D2.1 (K), D3.1 (K), D4.1 (K), J1.A1 (GND), J1.A12 (GND), J1.B1 (GND), J1.B12 (GND), J1.SH (SHIELD), J2.A1 (GND), J2.A12 (GND), J2.B1 (GND), J2.B12 (GND), J2.SH (SHIELD), J3.7, J5.6, J5.7, J7.3, J7.4, J8.3, J8.4, J9.3 (GND), J9.5 (GND), J9.9 (GNDDetect), J10.34, J10.36, J10.38, J10.40, R3.2, R4.2, R5.2, R9.2, R10.2, R11.2, R14.2, R15.2, R17.2, R19.2, SW1.2, SW2.2, U1.12 (VSS), U1.26 (VSS_USB), U1.45 (VSS), U1.63 (VSS), U1.83 (VSS), U1.89 (AVSS0/VREFL), U1.90 (VREFL0), U2.1 (A), U3.1 (A), U4.1 (GND), U5.4 (GND), U5.6 (SS_CTRL), U5.11 (GND), U6.2 (GND), U6.25 (GND), Y1.2 (G), Y1.4 (G)

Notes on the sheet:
EoS RA4M2 Board, rev A. Designed by Kartikeydheer Srivastava. Copyright (c) 2026 Kartikeydheer Srivastava. All rights reserved; see LICENSE.txt. 3.3 V logic; all header power pins are outputs. All expansion loads share 150 mA. JP1 fitted at reset selects SCI/USB boot. SWO and UART TXD9 share P109. 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

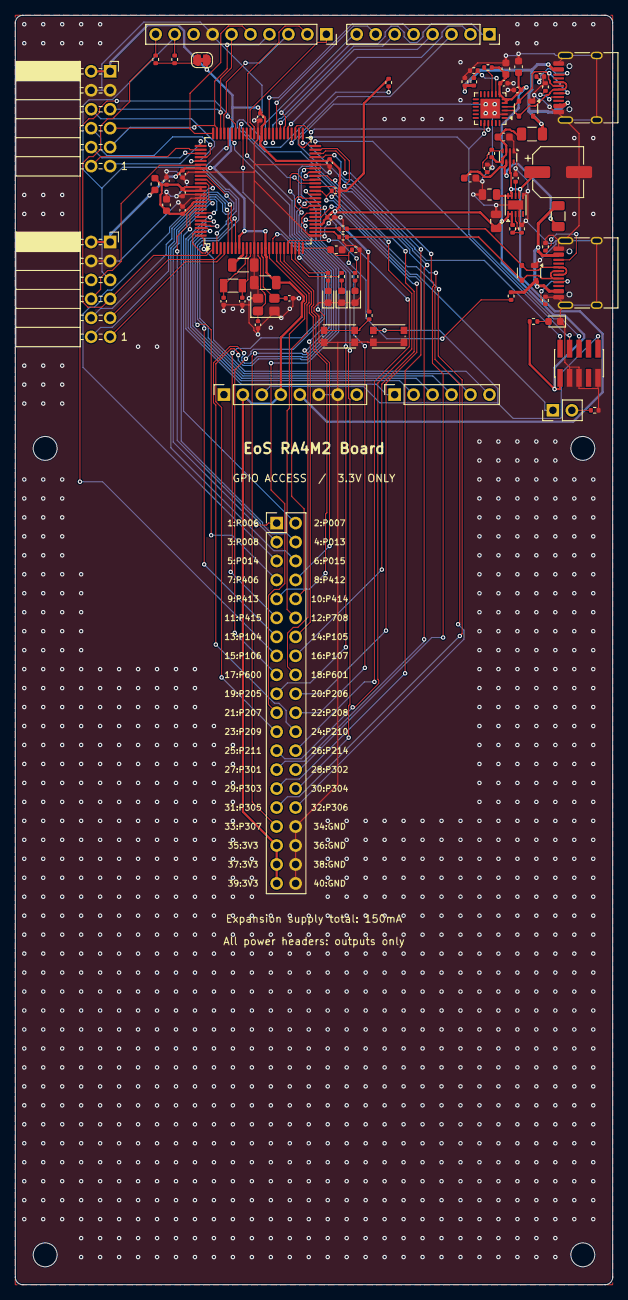
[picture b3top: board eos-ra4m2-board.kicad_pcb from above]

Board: 2 copper layers, 80.0 x 170.0 mm, 84 parts (0 on the bottom side), 111 nets.

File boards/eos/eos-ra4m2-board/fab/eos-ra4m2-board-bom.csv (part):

"Refs","Value","Footprint","Manufacturer","MPN","Description","Qty","DNP"
"C1","100n","Capacitor_SMD:C_1206_3216Metric","Samsung Electro-Mechanics","CL31B104KBCNNNC","Capacitor 100 nF 50 V X7R 10% 1206 (VCC pin 15 / VSS pin 12, 0.1 uF close to the pin, Renesas R01UH0892 Rev.1.50 Table 45.1)","1",""
"C2-C4,C6-C8,C16,C17","100n","Capacitor_SMD:C_0402_1005Metric","Samsung Electro-Mechanics","CL05B104KO5NNNC","Capacitor 100 nF 16 V X7R 0402 (AVCC0 pin 88 / AVSS0 pin 89, 0.1 uF, Renesas R01UH0892 Rev.1.50 Figure 37.34),Capacitor 100 nF 16 V X7R 0402 (CP2102N VIO/VDD pins 5 and 6, beside the pins, Silicon Labs CP2102N DS Rev. 1.5 Figure 2.3),Capacitor 100 nF 16 V X7R 0402 (CP2102N VREGIN pin 7, beside the pin, Silicon Labs CP2102N DS Rev. 1.5 Figure 2.3),Capacitor 100 nF 16 V X7R 0402 (VCC pin 46 / VSS pin 45, Renesas R01UH0892 Rev.1.50 Table 45.1),Capacitor 100 nF 16 V X7R 0402 (VCC pin 62 / VSS pin 63, Renesas R01UH0892 Rev.1.50 Table 45.1),Capacitor 100 nF 16 V X7R 0402 (VCC pin 82 / VSS pin 83, Renesas R01UH0892 Rev.1.50 Table 45.1),Capacitor 100 nF 16 V X7R 0402 (VCC_USB pin 29 to VSS_USB, close to VCC_USB, Renesas R01AN5988 Rev.1.04 Table 1),Capacitor 100 nF 16 V X7R 0402 (VREFH0 pin 91 / VREFL0 pin 90, 0.1 uF, Renesas R01UH0892 Rev.1.50 Figure 37.34)","8",""
"C5","220n","Capacitor_SMD:C_1206_3216Metric","Murata","GRM31C5C1H224JE02L","Capacitor 0.22 uF 50 V C0G 5% 1206 (VCL pin 9, stable nominal capacitance without X7R DC-bias loss, Renesas R01UH0892 Rev.1.50 Table 45.1)","1",""
"C9","10u","Capacitor_SMD:C_0603_1608Metric","Murata","GRM188R61A106KE69D","Capacitor 10 uF 10 V X5R 0603 (AVCC0 supply, reference value, Renesas R01UH0892 Rev.1.50 Figure 37.34)","1",""
"C10,C25","10n","Capacitor_SMD:C_0402_1005Metric","Murata","GRM155R71H103KA88D","Capacitor 10 nF 50 V X7R 0402 (AVCC0 supply, reference value 0.01 uF, Renesas R01UH0892 Rev.1.50 Figure 37.34),Capacitor 10 nF 50 V X7R 0402 +-10% (TPS7A91 NR/SS: tSS = 0.8 V x 9-11 nF / 9.0-4.0 uA = 0.80-2.2 ms, TI SBVS282A Eq. 6 and 5.5)","2",""
"C11,C12","6p","Capacitor_SMD:C_0402_1005Metric","Murata","GRM1555C1H6R0DA01D","Capacitor 6 pF 50 V C0G 0402 (EXTAL load CL1 for an 8 pF 16 MHz crystal, Renesas R01AN7202 Rev.1.02 Table 4.1.1),Capacitor 6 pF 50 V C0G 0402 (XTAL load CL2 for an 8 pF 16 MHz crystal, Renesas R01AN7202 Rev.1.02 Table 4.1.1)","2",""
"C13,C14","15p","Capacitor_SMD:C_0402_1005Metric","Murata","GRM1555C1H150JA01D","Capacitor 15 pF 50 V C0G 0402 (XCIN load CL1 for a 9 pF crystal, Renesas R01AN7202 Rev.1.02 Table 4.2.1),Capacitor 15 pF 50 V C0G 0402 (XCOUT load CL2 for a 9 pF crystal, Renesas R01AN7202 Rev.1.02 Table 4.2.1)","2",""
"C15,C20,C21","1u","Capacitor_SMD:C_0603_1608Metric","Murata","GRM188R71C105KA12D","Capacitor 1 uF 16 V X7R 0603 (TPS2116 VIN1, TI SLVSFG1A section 9),Capacitor 1 uF 16 V X7R 0603 (TPS2116 VIN2, TI SLVSFG1A section 9),Capacitor 1.0 uF 16 V X7R 0603 (USB_VBUS pin, Renesas R01UH0892 Rev.1.50 Figure 26.3)","3",""
"C18,C19","4.7u","Capacitor_SMD:C_0603_1608Metric","Murata","GRM188R61A475KE15D","Capacitor 4.7 uF 10 V X5R 0603 (CP2102N VIO, Silicon Labs CP2102N DS Rev. 1.5 section 2.1),Capacitor 4.7 uF 10 V X5R 0603 (CP2102N VREGIN/VDD, Silicon Labs CP2102N DS Rev. 1.5 Figure 2.3)","2",""
"C22","100u","Capacitor_SMD:CP_Elec_6.3x5.9","Panasonic","16SVPC100M","Polarized polymer capacitor 100 uF 16 V 20%, 24 mohm ESR, C6 case (Panasonic SVPC datasheet; TPS2116 VOUT, TI SLVSFG1A 7.3.4 and 8.2.2); pad 1 positive","1",""
"C23","22u","Capacitor_SMD:C_0805_2012Metric","Murata","GRM21BR61A226ME51L","Capacitor 22 uF 10 V X5R 0805 (TPS7A91 input, 10 uF or more, TI SBVS282A 5.3 and 7.1.3)","1",""
"C24","10u","Capacitor_SMD:C_0805_2012Metric","Murata","GRM21BR61C106KE15L","Capacitor 10 uF 16 V X5R 0805 (TPS7A91 output, 10 uF or more, TI SBVS282A 5.3 and 7.1.3)","1",""
"D1","PWR","LED_SMD:LED_0603_1608Metric","Kingbright","APTD1608LCGCK","LED green 0603, VF 1.9 V typ at 2 mA (Kingbright DSAO7432): power (3.3 V)","1",""
"D2","LED1","LED_SMD:LED_0603_1608Metric","Kingbright","APTD1608LSURCK","LED red 0603, VF 1.75 V typ at 2 mA (Kingbright DSAO7433): user LED1 (P409)","1",""
"D3","LED2","LED_SMD:LED_0603_1608Metric","Kingbright","APTD1608LCGCK","LED green 0603, VF 1.9 V typ at 2 mA (Kingbright DSAO7432): user LED2 (P410)","1",""
"D4","LED3","LED_SMD:LED_0603_1608Metric","Kingbright","APTD1608LSYCK","LED yellow 0603, VF 1.85 V typ at 2 mA (Kingbright DSAO7434): user LED3 (P411)","1",""
"F1,F2","500mA","Fuse:Fuse_1206_3216Metric","Littelfuse","1206L050YR","PTC fuse 0.50 A hold (0.42 A at 40 C), 1.00 A trip, 6 V, R1max 0.70 ohm, 1206, debug port (Littelfuse 1206L),PTC fuse 0.50 A hold (0.42 A at 40 C), 1.00 A trip, 6 V, R1max 0.70 ohm, 1206, device port (Littelfuse 1206L)","2",""
"FB1","220R","Inductor_SMD:L_0603_1608Metric","Bourns","MH1608-221Y","Ferrite bead 220 ohm at 100 MHz, 100 mohm, 2 A, 0603: AVCC0 filter (Bourns MH1608)","1",""
"J1,J2","USB-C","Connector_USB:USB_C_Receptacle_HRO_TYPE-C-31-M-12","Korean Hroparts","TYPE-C-31-M-12","USB-C 2.0 receptacle, 16 pins: USB, the RA4M2's own full-speed device port (USBFS),USB-C 2.0 receptacle, 16 pins: debug UART and serial programming (CP2102N on SCI9)","2",""
"J3","D8-SCL","Connector_PinSocket_2.54mm:PinSocket_1x10_P2.54mm_Vertical","Samtec","SSW-110-01-T-S","Socket 1x10 2.54 mm, Uno R3 digital D8-D13, GND, AREF (not connected), SDA, SCL (pin 1 = D8), 3.3 V logic","1",""
"J4","D0-D7","Connector_PinSocket_2.54mm:PinSocket_1x08_P2.54mm_Vertical","Samtec","SSW-108-01-T-S","Socket 1x8 2.54 mm, Uno R3 digital D0-D7 (pin 1 = D0), 3.3 V logic","1",""
"J5","POWER","Connector_PinSocket_2.54mm:PinSocket_1x08_P2.54mm_Vertical","Samtec","SSW-108-01-T-S","Socket 1x8 2.54 mm, Uno R3 power: NC, IOREF (3.3 V), RESET, 3V3, 5V, GND, GND, VIN (not connected)","1",""
"J6","A0-A5","Connector_PinSocket_2.54mm:PinSocket_1x06_P2.54mm_Vertical","Samtec","SSW-106-01-T-S","Socket 1x6 2.54 mm, Uno R3 analog A0-A5 (pin 1 = A0), 0-3.3 V","1",""
"J7","PMOD A","Connector_PinSocket_2.54mm:PinSocket_2x06_P2.54mm_Horizontal","Sullins","PPPC062LJBN-RC","Pmod host port, 2x6 right-angle female 2.54 mm, Type 2A expanded SPI, 3.3 V (Digilent Pmod Interface Specification (2020-09-29) sections 3-5, Figure 5); pad 1 = Pmod 6, pad 2 = Pmod 12, pad 3 = Pmod 5, pad 4 = Pmod 11, pad 5 = Pmod 4, pad 6 = Pmod 10, pad 7 = Pmod 3, pad 8 = Pmod 9, pad 9 = Pmod 2, pad 10 = Pmod 8, pad 11 = Pmod 1, pad 12 = Pmod 7","1",""
"J8","PMOD B","Connector_PinSocket_2.54mm:PinSocket_2x06_P2.54mm_Horizontal","Sullins","PPPC062LJBN-RC","Pmod host port, 2x6 right-angle female 2.54 mm, Type 6A expanded I2C, pin 10 open, 3.3 V (Digilent Pmod Interface Specification (2020-09-29) sections 3-5, Figure 5); pad 1 = Pmod 6, pad 2 = Pmod 12, pad 3 = Pmod 5, pad 4 = Pmod 11, pad 5 = Pmod 4, pad 6 = Pmod 10, pad 7 = Pmod 3, pad 8 = Pmod 9, pad 9 = Pmod 2, pad 10 = Pmod 8, pad 11 = Pmod 1, pad 12 = Pmod 7","1",""
"J9","SWD","Connector_PinHeader_1.27mm:PinHeader_2x05_P1.27mm_Vertical_SMD","Samtec","FTSH-105-01-L-DV-K","Arm Cortex Debug 10-pin, 1.27 mm: SWDIO P108, SWCLK P300, SWO P109, RES (Renesas R01AN5988 Rev.1.04 Figure 1, Renesas R01UH0892 Rev.1.50 Table 44.32); replaces the J-Link OB","1",""
"J10","GPIO ACCESS","Connector_PinHeader_2.54mm:PinHeader_2x20_P2.54mm_Vertical","Samtec","TSW-120-07-G-D","Original 2x20 GPIO access header; pin map from Renesas R01DS0367 Table 1.17; 3.3 V logic, shared power budget","1",""
"JP1","MD","Connector_PinHeader_2.54mm:PinHeader_1x02_P2.54mm_Vertical","Samtec","TSW-102-07-G-S","Pin header 1x2 2.54 mm, fitted with a Samtec SNT-100-BK-G 2.54 mm shunt at reset = SCI/USB boot mode (Renesas R01UH0892 Rev.1.50 Table 3.1; Renesas R01AN5988 Rev.1.04 Figure 8)","1",""
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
